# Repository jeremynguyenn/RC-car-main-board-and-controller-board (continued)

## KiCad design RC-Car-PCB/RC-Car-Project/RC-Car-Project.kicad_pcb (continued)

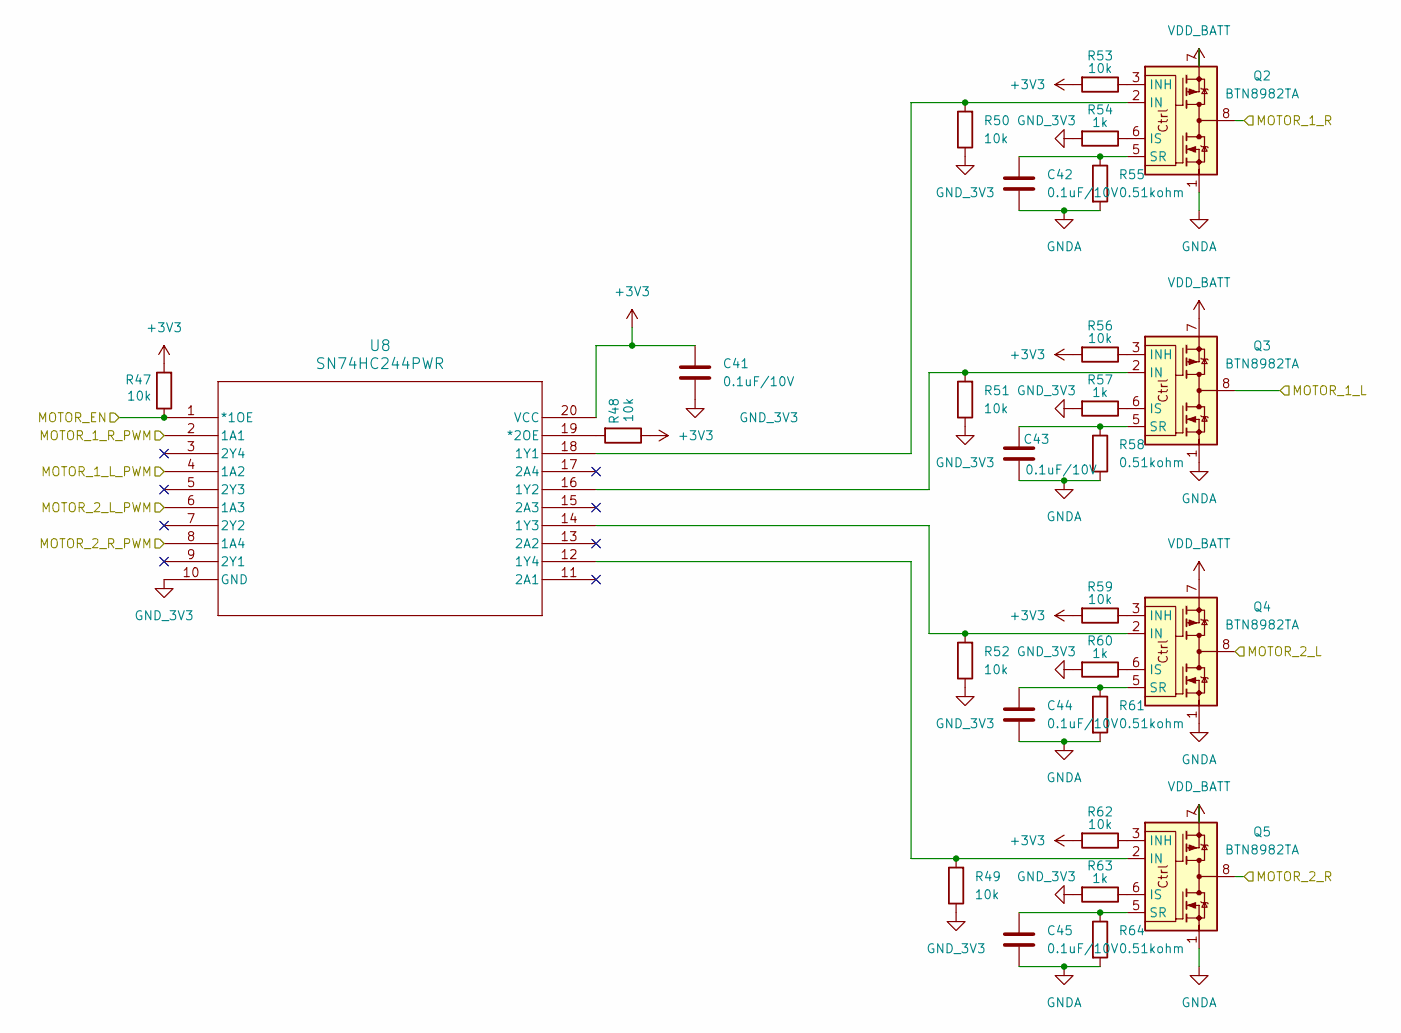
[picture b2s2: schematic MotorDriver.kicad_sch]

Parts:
C41, C42, C43, C44, C45: 0.1uF/10V; C_0603_1608Metric; MANUF_PN C0603C104K5RAC7411
Q2, Q3, Q4, Q5: BTN8982TA; TO-263-7_TabPin8; MANUF_PN BTN8982TAAUMA1
R47, R48, R49, R50, R51, R52, R53, R56, R59, R62: 10k; R_0603_1608Metric; MANUF_PN RC0603FR-0710KL
R54, R57, R60, R63: 1k; R_0603_1608Metric; MANUF_PN RMCF0603FT1K00
R55, R58, R61, R64: 0.51kohm; R_0603_1608Metric; MANUF_PN RMCF0603FT510R
U8: SN74HC244PWR; PW20; MANUF_PN SN74HC244PWR

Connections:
+3V3: C41.1, R47.2, R48.1, R53.2, R56.2, R59.2, R62.2, U8.20 (VCC); also elsewhere on the board
/Connectors/M1_LEFT: Q3.4, Q3.8; also elsewhere on the board
/Connectors/M1_RIGHT: Q2.4, Q2.8; also elsewhere on the board
/Connectors/M2_LEFT: Q4.4, Q4.8; also elsewhere on the board
/Connectors/M2_RIGHT: Q5.4, Q5.8; also elsewhere on the board
/MCU/LEFT_PWM1: U8.4 (1A2); also elsewhere on the board
/MCU/LEFT_PWM2: U8.6 (1A3); also elsewhere on the board
/MCU/MOTOR_EN: R47.1, U8.1 (*1OE); also elsewhere on the board
/MCU/RIGHT_PWM1: U8.2 (1A1); also elsewhere on the board
/MCU/RIGHT_PWM2: U8.8 (1A4); also elsewhere on the board
GNDA: C41.2, C42.2, C43.2, C44.2, C45.2, Q2.1, Q3.1, Q4.1, Q5.1, R49.1, R50.1, R51.1, R52.1, R54.2, R55.2, R57.2, R58.2, R60.2, R61.2, R63.2, R64.2, U8.10 (GND); also elsewhere on the board
unnamed: Q2.2 (IN), R50.2, U8.18 (1Y1)
unnamed: Q2.3 (INH), R53.1
unnamed: Q2.6 (IS), R54.1
unnamed: C42.1, Q2.5 (SR), R55.1
unnamed: Q3.2 (IN), R51.2, U8.16 (1Y2)
unnamed: Q3.3 (INH), R56.1
unnamed: Q3.6 (IS), R57.1
unnamed: C43.1, Q3.5 (SR), R58.1
unnamed: Q4.2 (IN), R52.2, U8.14 (1Y3)
unnamed: Q4.3 (INH), R59.1
unnamed: Q4.6 (IS), R60.1
unnamed: C44.1, Q4.5 (SR), R61.1
unnamed: Q5.2 (IN), R49.2, U8.12 (1Y4)
unnamed: Q5.3 (INH), R62.1
unnamed: Q5.6 (IS), R63.1
unnamed: C45.1, Q5.5 (SR), R64.1
unnamed: R48.2, U8.19 (*2OE)
VDD_BATT: Q2.7, Q3.7, Q4.7, Q5.7; also elsewhere on the board

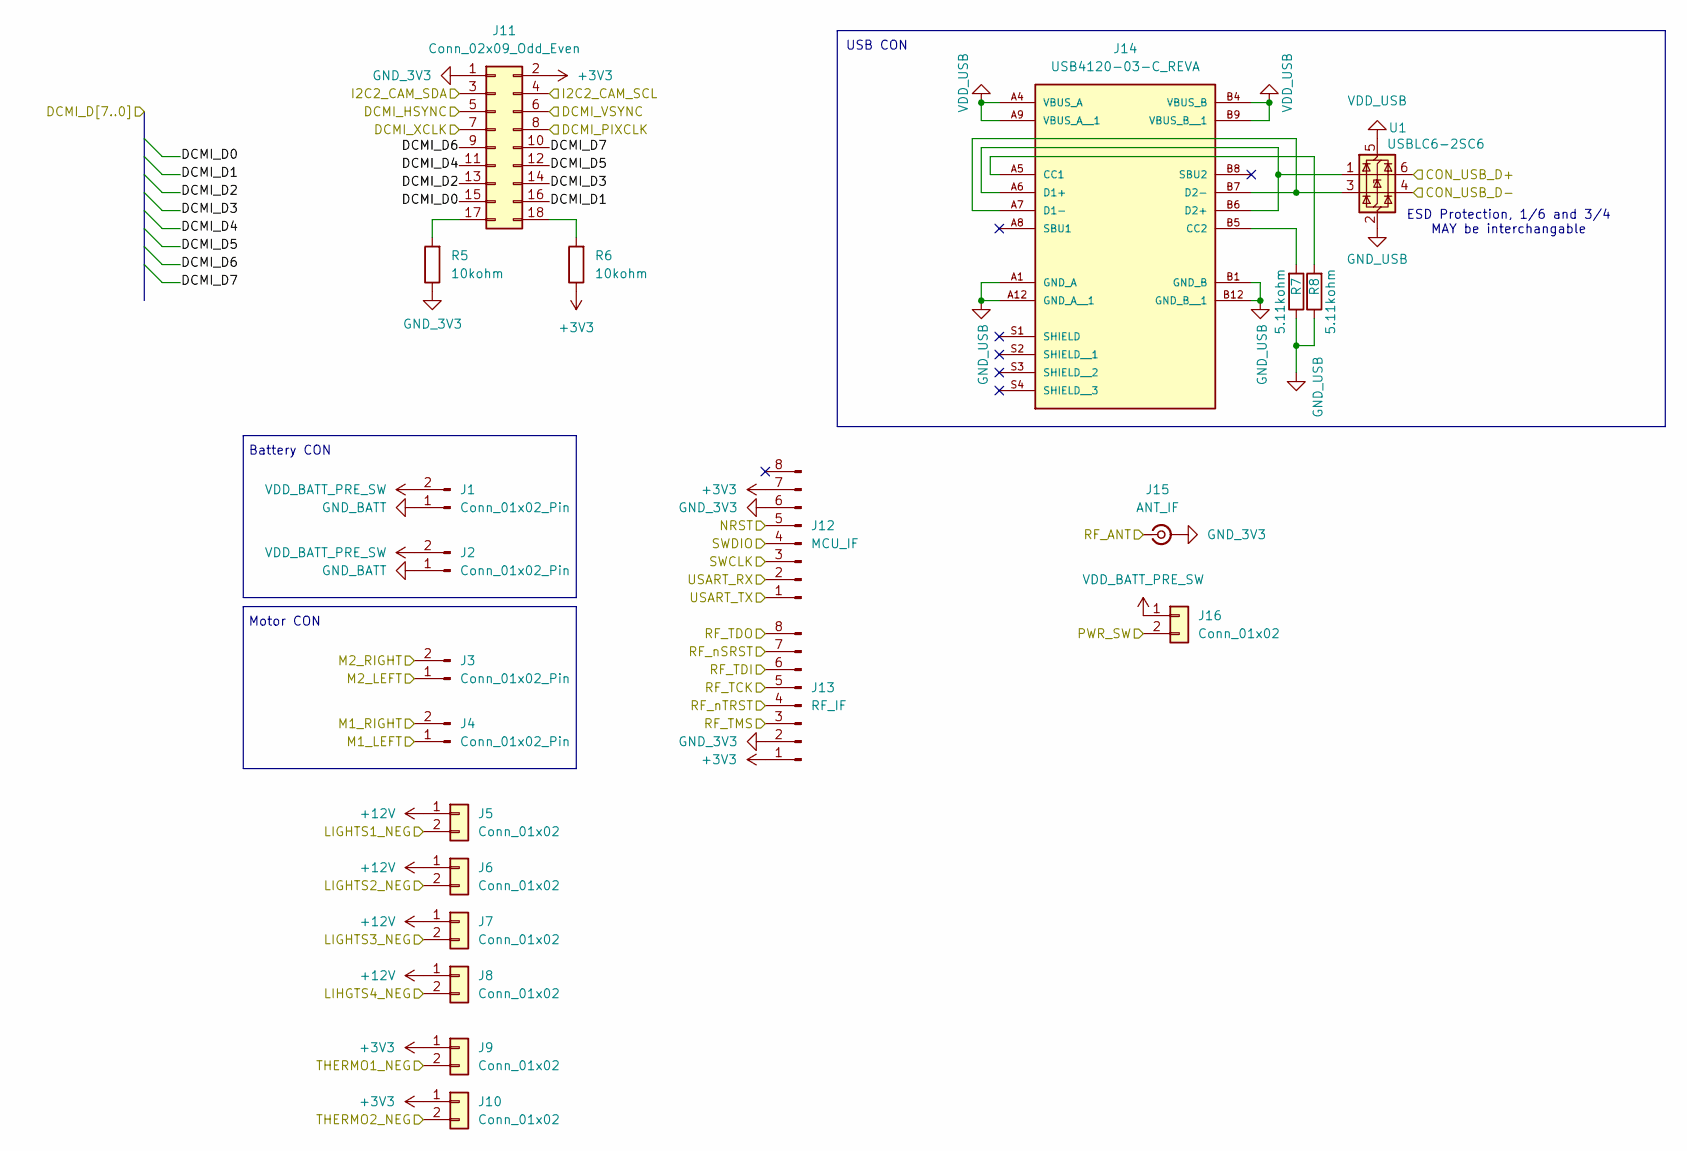
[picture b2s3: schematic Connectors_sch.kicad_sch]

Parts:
J1, J2, J3, J4: Conn_01x02_Pin; AMASS_XT60-M_1x02_P7.20mm_Vertical; MANUF_PN N/A
J5, J6, J7, J8, J9, J10, J16: Conn_01x02; JST_XH_B2B-XH-AM_1x02_P2.50mm_Vertical; MANUF_PN B2B-XH-AM
J11: Conn_02x09_Odd_Even; PinSocket_2x09_P2.54mm_Horizontal; MANUF_PN PPPC092LJBN-RC
J12: MCU_IF; PinHeader_2x04_P2.54mm_Vertical; MANUF_PN PH2-08-UA
J13: RF_IF; PinHeader_2x04_P2.54mm_Vertical; MANUF_PN PH2-08-UA
J14: USB4120-03-C_REVA; GCT_USB4120-03-C_REVA; PARTREV A
J15: ANT_IF; SMA_Molex_73251-1153_EdgeMount_Horizontal; MANUF_PN 0732511153
R5, R6: 10kohm; R_0603_1608Metric; MANUF_PN RC0603FR-0710KL
R7, R8: 5.11kohm; R_0603_1608Metric; MANUF_PN CRCW06035K11FKEAC
U1: USBLC6-2SC6; SOT-23-6; MANUF_PN USBLC6-2SC6

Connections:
+3V3: J9.1, J10.1, J11.2, J12.7, J13.1, R6.1; also elsewhere on the board
+12V: J5.1, J6.1, J7.1, J8.1; also elsewhere on the board
/Connectors/CON_USB_D+: U1.6 (I/O1); also elsewhere on the board
/Connectors/CON_USB_D-: U1.4 (I/O2); also elsewhere on the board
/Connectors/DCMI_D0: J11.15; also elsewhere on the board
/Connectors/DCMI_D1: J11.16; also elsewhere on the board
/Connectors/DCMI_D2: J11.13; also elsewhere on the board
/Connectors/DCMI_D3: J11.14; also elsewhere on the board
/Connectors/DCMI_D4: J11.11; also elsewhere on the board
/Connectors/DCMI_D5: J11.12; also elsewhere on the board
/Connectors/DCMI_D6: J11.9; also elsewhere on the board
/Connectors/DCMI_D7: J11.10; also elsewhere on the board
/Connectors/DCMI_HSYNC: J11.5; also elsewhere on the board
/Connectors/DCMI_PIXCLK: J11.8; also elsewhere on the board
/Connectors/DCMI_VSYNC: J11.6; also elsewhere on the board
/Connectors/DCMI_XCLK: J11.7; also elsewhere on the board
/Connectors/I2C2_CAM_SCL: J11.4; also elsewhere on the board
/Connectors/I2C2_CAM_SDA: J11.3; also elsewhere on the board
/Connectors/LIGHTS1_NEG: J5.2; also elsewhere on the board
/Connectors/LIGHTS2_NEG: J6.2; also elsewhere on the board
/Connectors/LIGHTS3_NEG: J7.2; also elsewhere on the board
/Connectors/LIHGTS4_NEG: J8.2; also elsewhere on the board
/Connectors/M1_LEFT: J4.1; also elsewhere on the board
/Connectors/M1_RIGHT: J4.2; also elsewhere on the board
/Connectors/M2_LEFT: J3.1; also elsewhere on the board
/Connectors/M2_RIGHT: J3.2; also elsewhere on the board
/Connectors/NRST: J12.5; also elsewhere on the board
/Connectors/PWR_SW: J16.2; also elsewhere on the board
/Connectors/RF_ANT: J15.1 (In); also elsewhere on the board
/Connectors/RF_TCK: J13.5; also elsewhere on the board
/Connectors/RF_TDI: J13.6; also elsewhere on the board
/Connectors/RF_TDO: J13.8; also elsewhere on the board
/Connectors/RF_TMS: J13.3; also elsewhere on the board
/Connectors/RF_nSRST: J13.7
/Connectors/RF_nTRST: J13.4; also elsewhere on the board
/Connectors/SWCLK: J12.3; also elsewhere on the board
/Connectors/SWDIO: J12.4; also elsewhere on the board
/Connectors/THERMO1_NEG: J9.2; also elsewhere on the board
/Connectors/THERMO2_NEG: J10.2; also elsewhere on the board
/Connectors/USART_RX: J12.2; also elsewhere on the board
/Connectors/USART_TX: J12.1; also elsewhere on the board
GNDA: J11.1, J12.6, J13.2, J14.A1 (GND_A), J14.A12 (GND_A__1), J14.B1 (GND_B), J14.B12 (GND_B__1), J15.2 (Ext), R5.1, R7.1, R8.1, U1.2 (GND); also elsewhere on the board
GND_BATT: J1.1, J2.1; also elsewhere on the board
unnamed: J11.17, R5.2
unnamed: J11.18, R6.2
unnamed: J14.A5 (CC1), R8.2
unnamed: J14.B5 (CC2), R7.2
unnamed: J14.A6 (D1+), J14.B6 (D2+), U1.1 (I/O1)
unnamed: J14.A7 (D1-), J14.B7 (D2-), U1.3 (I/O2)
VDD_BATT_PRE_SW: J1.2, J2.2, J16.1; also elsewhere on the board
VDD_USB: J14.A4 (VBUS_A), J14.A9 (VBUS_A__1), J14.B4 (VBUS_B), J14.B9 (VBUS_B__1), U1.5 (VBUS); also elsewhere on the board

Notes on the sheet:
Battery CON
ESD Protection, 1/6 and 3/4 MAY be interchangable
USB CON
Motor CON

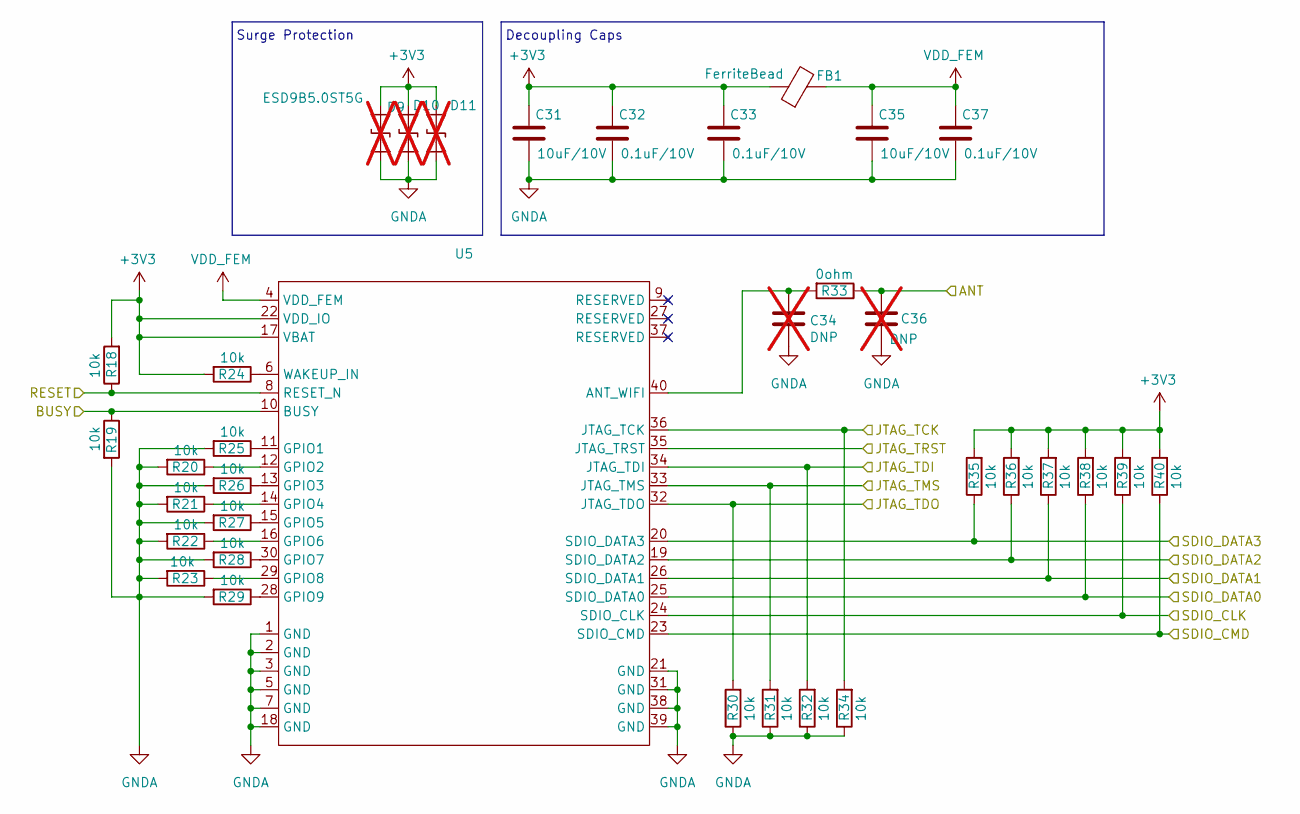
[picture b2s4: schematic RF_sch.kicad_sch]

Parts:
C31, C35: 10uF/10V; C_0603_1608Metric; MANUF_PN CL10A106KP8NNNC
C32, C33, C37: 0.1uF/10V; C_0603_1608Metric; MANUF_PN C0603C104K5RAC7411
C34, C36: DNP; C_0603_1608Metric; MANUF_PN N/A; not fitted
D9, D10, D11: ESD9B5.0ST5G; D_SOD-923; MANUF_PN N/A; not fitted
FB1: FerriteBead; C_0603_1608Metric; MANUF_PN HCB 1608KF-181T20
R18, R19, R20, R21, R22, R23, R24, R25, R26, R27, R28, R29, R30, R31, R32, R34, R35, R36, R37, R38, R39, R40: 10k; C_0603_1608Metric; MANUF_PN RC0603FR-0710KL
R33: 0ohm; R_0603_1608Metric; MANUF_PN RMCF0603ZT0R00
U5: FGH100MABMD; MANUF_PN FGH100MABMD

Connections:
+3V3: C31.1, C32.1, C33.1, D9.2 (A2), D10.2 (A2), D11.2 (A2), FB1.1, R18.2, R24.2, R35.2, R36.2, R37.2, R38.2, R39.2, R40.2, U5.17 (VBAT), U5.22 (VDD_IO); also elsewhere on the board
/Connectors/RF_ANT: C36.1, R33.1; also elsewhere on the board
/Connectors/RF_TCK: R34.2, U5.36 (JTAG_TCK); also elsewhere on the board
/Connectors/RF_TDI: R32.2, U5.34 (JTAG_TDI); also elsewhere on the board
/Connectors/RF_TDO: R30.2, U5.32 (JTAG_TDO); also elsewhere on the board
/Connectors/RF_TMS: R31.2, U5.33 (JTAG_TMS); also elsewhere on the board
/Connectors/RF_nTRST: U5.35 (JTAG_TRST); also elsewhere on the board
/MCU/RF_RESET: R18.1, U5.8 (RESET_N); also elsewhere on the board
/MCU/SDMMC1_CK: R39.1, U5.24 (SDIO_CLK); also elsewhere on the board
/MCU/SDMMC1_CMD: R40.1, U5.23 (SDIO_CMD); also elsewhere on the board
/MCU/SDMMC1_D0: R38.1, U5.25 (SDIO_DATA0); also elsewhere on the board
/MCU/SDMMC1_D1: R37.1, U5.26 (SDIO_DATA1); also elsewhere on the board
/MCU/SDMMC1_D2: R36.1, U5.19 (SDIO_DATA2); also elsewhere on the board
/MCU/SDMMC1_D3: R35.1, U5.20 (SDIO_DATA3); also elsewhere on the board
/RF/BUSY: R19.1, U5.10 (BUSY)
GNDA: C31.2, C32.2, C33.2, C34.2, C35.2, C36.2, C37.2, D9.1 (A1), D10.1 (A1), D11.1 (A1), R19.2, R20.2, R21.2, R22.2, R23.2, R25.2, R26.2, R27.2, R28.2, R29.2, R30.1, R31.1, R32.1, R34.1, U5.1 (GND), U5.2 (GND), U5.3 (GND), U5.5 (GND), U5.7 (GND), U5.18 (GND), U5.21 (GND), U5.31 (GND), U5.38 (GND), U5.39 (GND); also elsewhere on the board
unnamed: C34.1, R33.2, U5.40 (ANT_WIFI)
unnamed: R25.1, U5.11 (GPIO1)
unnamed: R20.1, U5.12 (GPIO2)
unnamed: R26.1, U5.13 (GPIO3)
unnamed: R21.1, U5.14 (GPIO4)
unnamed: R27.1, U5.15 (GPIO5)
unnamed: R22.1, U5.16 (GPIO6)
unnamed: R28.1, U5.30 (GPIO7)
unnamed: R23.1, U5.29 (GPIO8)
unnamed: R29.1, U5.28 (GPIO9)
unnamed: R24.1, U5.6 (WAKEUP_IN)
VDD_FEM: C35.1, C37.1, FB1.2, U5.4 (VDD_FEM)

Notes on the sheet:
Decoupling Caps
Surge Protection

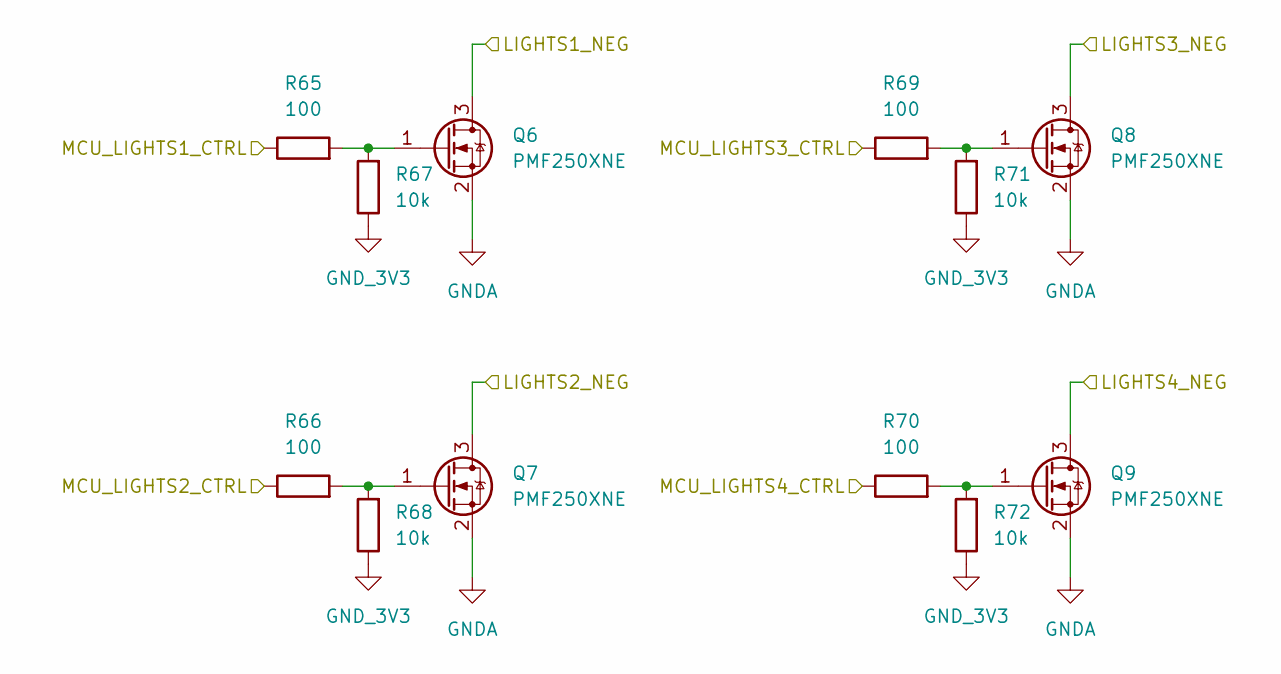
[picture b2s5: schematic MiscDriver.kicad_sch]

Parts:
Q6, Q7, Q8, Q9: PMF250XNE; SOT-23; MANUF_PN PMF250XNEX
R65, R66, R69, R70: 100; R_0603_1608Metric; MANUF_PN RC0603FR-07100RL
R67, R68, R71, R72: 10k; R_0603_1608Metric; MANUF_PN RC0603FR-0710KL

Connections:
/Connectors/LIGHTS1_NEG: Q6.3 (D); also elsewhere on the board
/Connectors/LIGHTS2_NEG: Q7.3 (D); also elsewhere on the board
/Connectors/LIGHTS3_NEG: Q8.3 (D); also elsewhere on the board
/Connectors/LIHGTS4_NEG: Q9.3 (D); also elsewhere on the board
/MCU/LIGHTS1_PWM: R65.1; also elsewhere on the board
/MCU/LIGHTS2_PWM: R66.1; also elsewhere on the board
/MCU/LIGHTS3_PWM: R69.1; also elsewhere on the board
/MCU/LIGHTS4_PWM: R70.1; also elsewhere on the board
GNDA: Q6.2 (S), Q7.2 (S), Q8.2 (S), Q9.2 (S), R67.1, R68.1, R71.1, R72.1; also elsewhere on the board
unnamed: Q6.1 (G), R65.2, R67.2
unnamed: Q7.1 (G), R66.2, R68.2
unnamed: Q8.1 (G), R69.2, R71.2
unnamed: Q9.1 (G), R70.2, R72.2

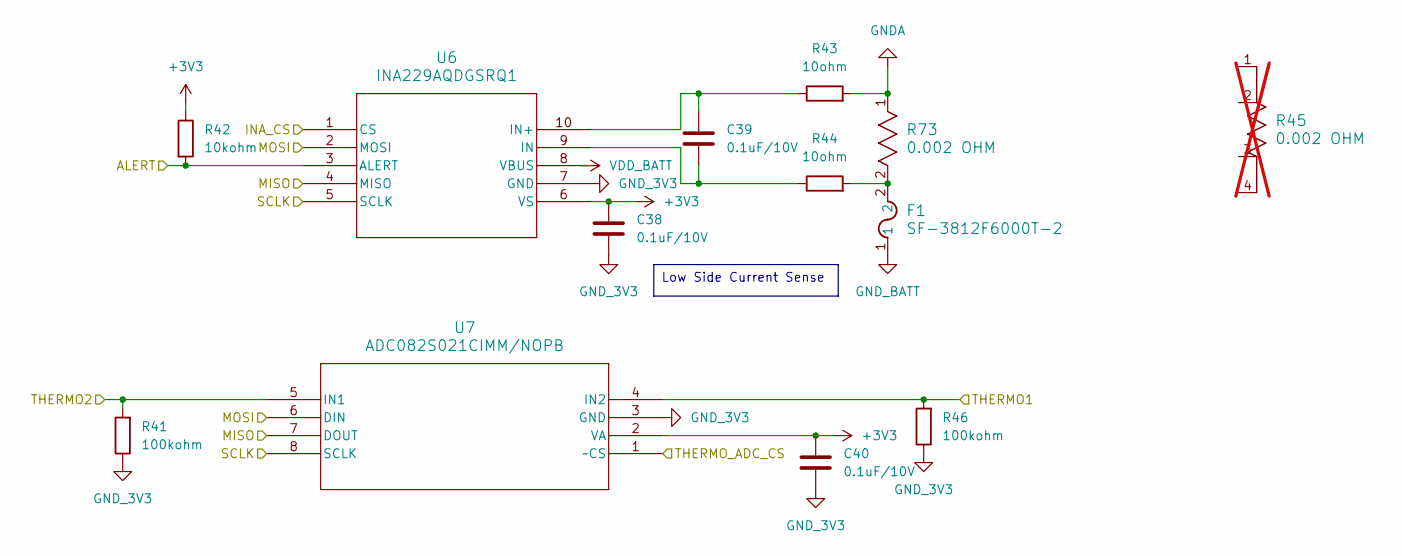
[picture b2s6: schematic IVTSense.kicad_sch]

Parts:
C38, C39, C40: 0.1uF/10V; C_0603_1608Metric; MANUF_PN C0603C104K5RAC7411
F1: SF-3812F6000T-2; FUS_SF-3812F_BRN; MANUF_PN SF-3812F6000T-2
R41, R46: 100kohm; R_0603_1608Metric; MANUF_PN RMCF0603FT100K
R42: 10kohm; R_0603_1608Metric; MANUF_PN RC0603FR-0710KL
R43, R44: 10ohm; R_0603_1608Metric; MANUF_PN RMCF0603FT10R0
R45: 0.002 OHM; WSL2726_VIS; MANUF_PN WSL27262L000FEB; not fitted
R73: 0.002 OHM; RES_WSLP5931_.002OHM_VIS; MANUF_PN WSLP59312L000FEA
U6: INA229AQDGSRQ1; VSSOP10_DGS_TEX; MANUF_PN INA229AQDGSRQ1
U7: ADC082S021CIMM/NOPB; MUA08A; MANUF_PN ADC082S021CIMM/NOPB

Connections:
+3V3: C38.1, C40.1, R42.1, U6.6 (VS), U7.2 (VA); also elsewhere on the board
/Connectors/THERMO1_NEG: R46.2, U7.4 (IN2); also elsewhere on the board
/Connectors/THERMO2_NEG: R41.2, U7.5 (IN1); also elsewhere on the board
/IVTSense/ALERT: R42.2, U6.3 (ALERT); also elsewhere on the board
/IVTSense/INA_CS: U6.1 (CS); also elsewhere on the board
/IVTSense/MISO: U6.4 (MISO), U7.7 (DOUT); also elsewhere on the board
/IVTSense/MOSI: U6.2 (MOSI), U7.6 (DIN); also elsewhere on the board
/IVTSense/SCLK: U6.5 (SCLK), U7.8 (SCLK); also elsewhere on the board
/IVTSense/THERMO_ADC_CS: U7.1 (~CS); also elsewhere on the board
GNDA: C38.2, C40.2, R41.1, R43.2, R46.1, R73.1, U6.7 (GND), U7.3 (GND); also elsewhere on the board
GND_BATT: F1.1; also elsewhere on the board
unnamed: F1.2, R44.2, R73.2
unnamed: C39.2, R44.1, U6.9 (IN)
unnamed: C39.1, R43.1, U6.10 (IN+)
VDD_BATT: U6.8 (VBUS); also elsewhere on the board

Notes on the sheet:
Low Side Current Sense

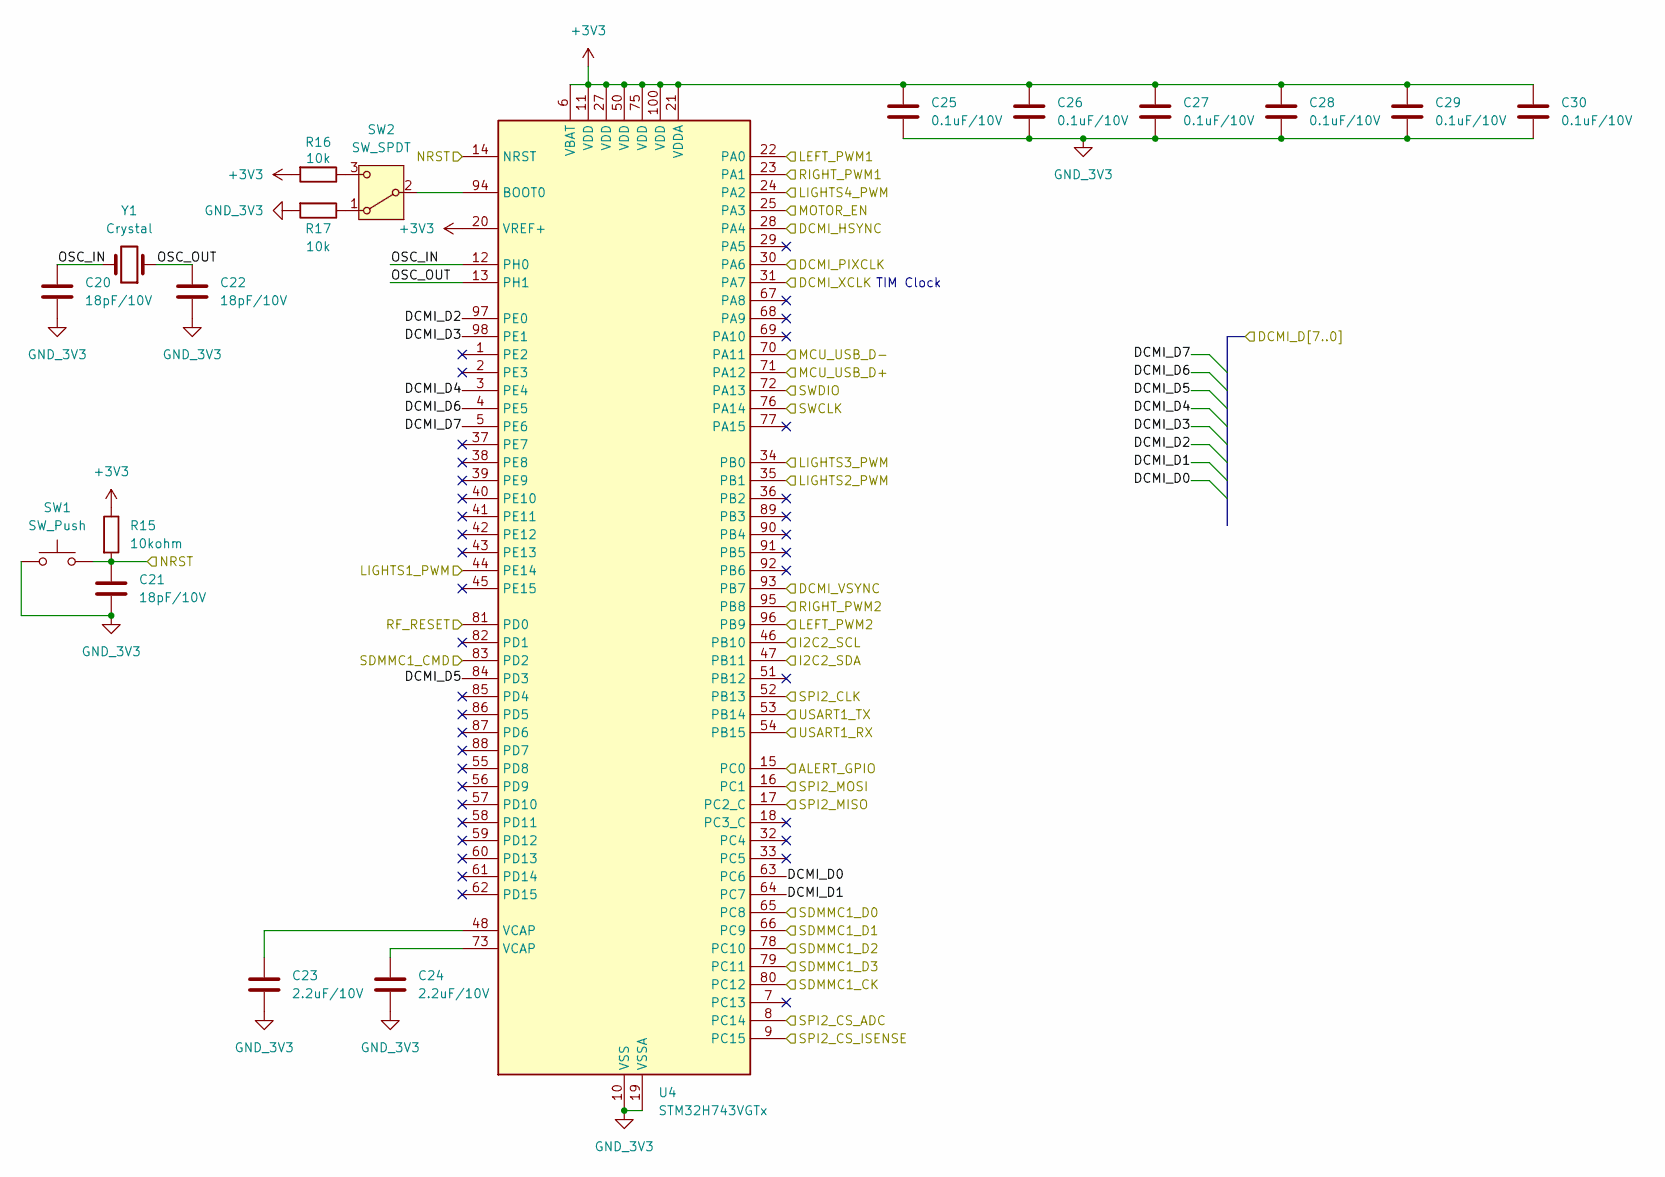
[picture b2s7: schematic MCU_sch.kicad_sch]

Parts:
C20, C21, C22: 18pF/10V; C_0603_1608Metric; MANUF_PN C0603C180J5GACTU
C23, C24: 2.2uF/10V; C_0603_1608Metric; MANUF_PN C0603C225K4PACTU
C25, C26, C27, C28, C29, C30: 0.1uF/10V; C_0603_1608Metric; MANUF_PN C0603C104K5RAC7411
R15: 10kohm; R_0603_1608Metric; MANUF_PN RC0603FR-0710KL
R16, R17: 10k; C_0603_1608Metric; MANUF_PN RC0603FR-0710KL
SW1: SW_Push; SW_PUSH_6mm; MANUF_PN 1825910-6
SW2: SW_SPDT; PinHeader_1x03_P2.54mm_Vertical; MANUF_PN N/A
U4: STM32H743VGTx; LQFP-100_14x14mm_P0.5mm; MANUF_PN STM32H743VGT6
Y1: Crystal; Crystal_SMD_Abracon_ABM3-2Pin_5.0x3.2mm; MANUF_PN ABM7-25.000MHZ-D2Y-T

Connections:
+3V3: C25.1, C26.1, C27.1, C28.1, C29.1, C30.1, R15.1, R16.2, U4.6 (VBAT), U4.11 (VDD), U4.20 (VREF+), U4.21 (VDDA), U4.27 (VDD), U4.50 (VDD), U4.75 (VDD), U4.100 (VDD); also elsewhere on the board
/Connectors/CON_USB_D+: U4.71 (PA12); also elsewhere on the board
/Connectors/CON_USB_D-: U4.70 (PA11); also elsewhere on the board
/Connectors/DCMI_D0: U4.63 (PC6); also elsewhere on the board
/Connectors/DCMI_D1: U4.64 (PC7); also elsewhere on the board
/Connectors/DCMI_D2: U4.97 (PE0); also elsewhere on the board
/Connectors/DCMI_D3: U4.98 (PE1); also elsewhere on the board
/Connectors/DCMI_D4: U4.3 (PE4); also elsewhere on the board
/Connectors/DCMI_D5: U4.84 (PD3); also elsewhere on the board
/Connectors/DCMI_D6: U4.4 (PE5); also elsewhere on the board
/Connectors/DCMI_D7: U4.5 (PE6); also elsewhere on the board
/Connectors/DCMI_HSYNC: U4.28 (PA4); also elsewhere on the board
/Connectors/DCMI_PIXCLK: U4.30 (PA6); also elsewhere on the board
/Connectors/DCMI_VSYNC: U4.93 (PB7); also elsewhere on the board
/Connectors/DCMI_XCLK: U4.31 (PA7); also elsewhere on the board
/Connectors/I2C2_CAM_SCL: U4.46 (PB10); also elsewhere on the board
/Connectors/I2C2_CAM_SDA: U4.47 (PB11); also elsewhere on the board
/Connectors/NRST: C21.1, R15.2, SW1.2, U4.14 (NRST); also elsewhere on the board
/Connectors/SWCLK: U4.76 (PA14); also elsewhere on the board
/Connectors/SWDIO: U4.72 (PA13); also elsewhere on the board
/Connectors/USART_RX: U4.54 (PB15); also elsewhere on the board
/Connectors/USART_TX: U4.53 (PB14); also elsewhere on the board
/IVTSense/ALERT: U4.15 (PC0); also elsewhere on the board
/IVTSense/INA_CS: U4.9 (PC15); also elsewhere on the board
/IVTSense/MISO: U4.17 (PC2_C); also elsewhere on the board
/IVTSense/MOSI: U4.16 (PC1); also elsewhere on the board
/IVTSense/SCLK: U4.52 (PB13); also elsewhere on the board
/IVTSense/THERMO_ADC_CS: U4.8 (PC14); also elsewhere on the board
/MCU/LEFT_PWM1: U4.22 (PA0); also elsewhere on the board
/MCU/LEFT_PWM2: U4.96 (PB9); also elsewhere on the board
/MCU/LIGHTS1_PWM: U4.44 (PE14); also elsewhere on the board
/MCU/LIGHTS2_PWM: U4.35 (PB1); also elsewhere on the board
/MCU/LIGHTS3_PWM: U4.34 (PB0); also elsewhere on the board
/MCU/LIGHTS4_PWM: U4.24 (PA2); also elsewhere on the board
/MCU/MOTOR_EN: U4.25 (PA3); also elsewhere on the board
/MCU/OSC_IN: C20.1, U4.12 (PH0), Y1.2
/MCU/OSC_OUT: C22.1, U4.13 (PH1), Y1.1
/MCU/RF_RESET: U4.81 (PD0); also elsewhere on the board
/MCU/RIGHT_PWM1: U4.23 (PA1); also elsewhere on the board
/MCU/RIGHT_PWM2: U4.95 (PB8); also elsewhere on the board
/MCU/SDMMC1_CK: U4.80 (PC12); also elsewhere on the board
/MCU/SDMMC1_CMD: U4.83 (PD2); also elsewhere on the board
/MCU/SDMMC1_D0: U4.65 (PC8); also elsewhere on the board
/MCU/SDMMC1_D1: U4.66 (PC9); also elsewhere on the board
/MCU/SDMMC1_D2: U4.78 (PC10); also elsewhere on the board
/MCU/SDMMC1_D3: U4.79 (PC11); also elsewhere on the board
GNDA: C20.2, C21.2, C22.2, C23.2, C24.2, C25.2, C26.2, C27.2, C28.2, C29.2, C30.2, R17.2, SW1.1, U4.10 (VSS), U4.19 (VSSA), U4.26 (VSS), U4.49 (VSS), U4.74 (VSS), U4.99 (VSS); also elsewhere on the board
unnamed: C23.1, U4.48 (VCAP)
unnamed: C24.1, U4.73 (VCAP)
unnamed: R17.1, SW2.1 (A)
unnamed: SW2.2 (B), U4.94 (BOOT0)
unnamed: R16.1, SW2.3 (C)

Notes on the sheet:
TIM Clock

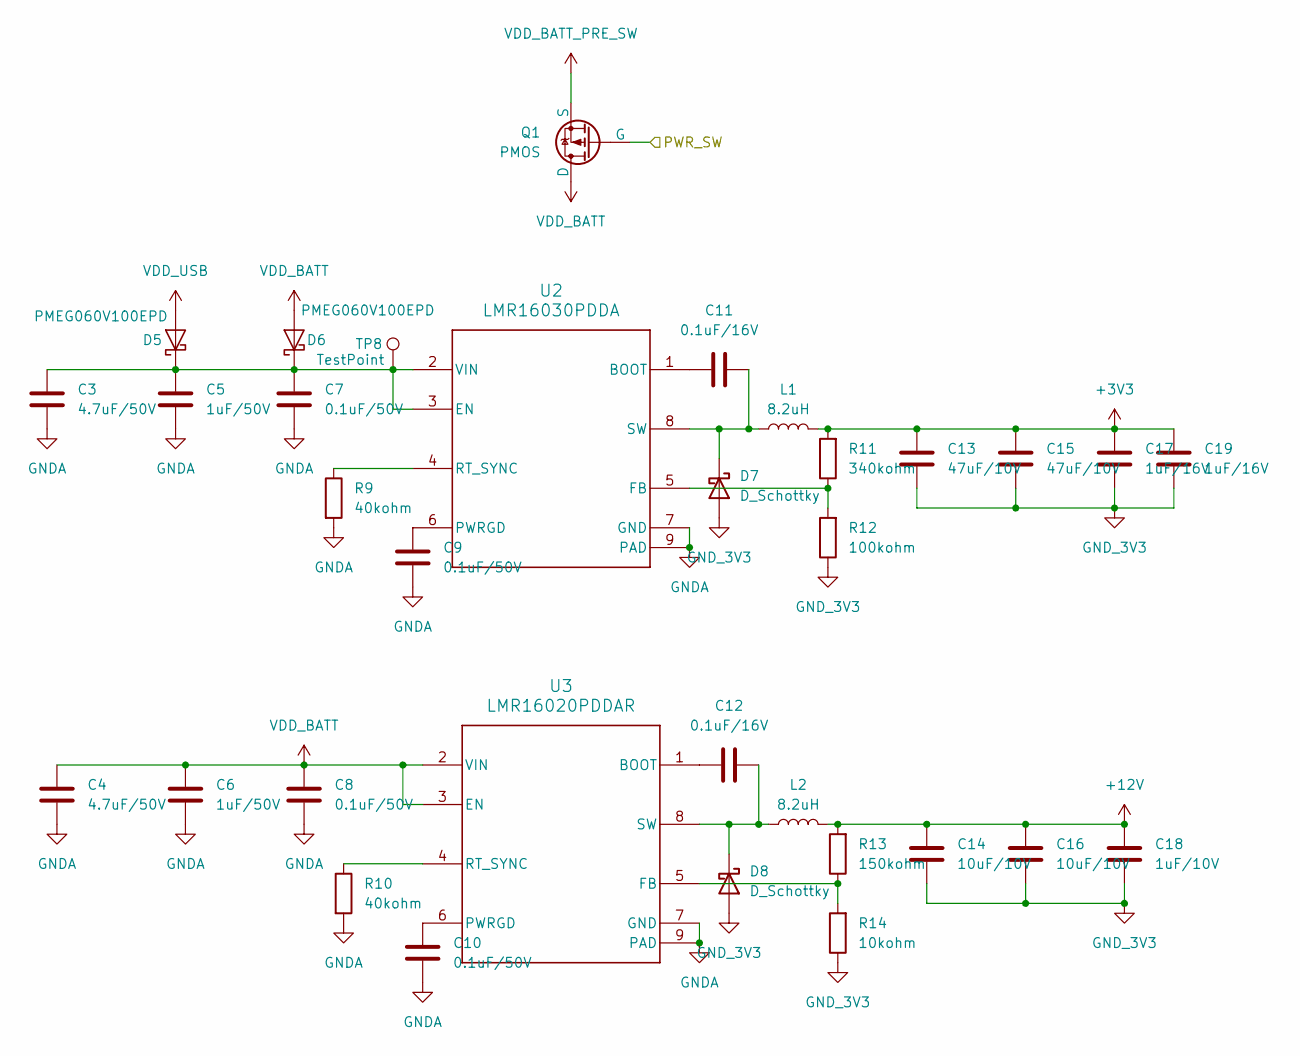
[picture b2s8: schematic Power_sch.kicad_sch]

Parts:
C3, C4: 4.7uF/50V; C_1210_3225Metric; MANUF_PN CL32B475KCVZW6E
C5, C6: 1uF/50V; C_0603_1608Metric; MANUF_PN GRM188D72A105KE01D
C7, C8, C9, C10: 0.1uF/50V; C_0603_1608Metric; MANUF_PN C0603C104K5RAC7411
C11, C12: 0.1uF/16V; C_0603_1608Metric; MANUF_PN C0603C104K5RAC7411
C13, C15: 47uF/10V; C_1210_3225Metric; MANUF_PN LMK325B7476MM-PR
C14, C16: 10uF/10V; C_0603_1608Metric; MANUF_PN CL10A106KP8NNNC
C17, C19: 1uF/16V; C_0603_1608Metric; MANUF_PN CL10B105KO8NNNC
C18: 1uF/10V; C_0603_1608Metric; MANUF_PN CL10B105KO8NNNC
D5, D6: PMEG060V100EPD; Nexperia_CFP15_SOT-1289; MANUF_PN PMEG060V100EPDZ
D7, D8: D_Schottky; Nexperia_CFP3_SOD-123W; MANUF_PN PMEG60T30ELR-QX
L1, L2: 8.2uH; L_Wuerth_MAPI-4030; MANUF_PN 74438357082
Q1: PMOS; TO-220-3_Horizontal_TabDown; MANUF_PN SPP80P06PHXKSA1
R9, R10: 40kohm; R_0603_1608Metric; MANUF_PN RT0603BRD0740KL
R11: 340kohm; R_0603_1608Metric; MANUF_PN RMCF0603FT340K
R12: 100kohm; R_0603_1608Metric; MANUF_PN RMCF0603FT100K
R13: 150kohm; R_0603_1608Metric; MANUF_PN RMCF0603FG150K
R14: 10kohm; R_0603_1608Metric; MANUF_PN RC0603FR-0710KL
TP8: TestPoint; PinHeader_1x02_P2.54mm_Vertical; MANUF_PN N/A
U2: LMR16030PDDA; DDA0008E_N; MANUF_PN LMR16030PDDA
U3: LMR16020PDDAR; DDA0008E_N; MANUF_PN LMR16020PDDAR

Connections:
+3V3: C13.1, C15.1, C17.1, C19.1, L1.2, R11.2; also elsewhere on the board
+12V: C14.1, C16.1, C18.1, L2.2, R13.2; also elsewhere on the board
/Connectors/PWR_SW: Q1.2 (G); also elsewhere on the board
GNDA: C3.2, C4.2, C5.2, C6.2, C7.2, C8.2, C9.2, C10.2, C13.2, C14.2, C15.2, C16.2, C17.2, C18.2, C19.2, D7.2 (A), D8.2 (A), R9.2, R10.2, R12.1, R14.1, U2.7 (GND), U2.9 (PAD), U3.7 (GND), U3.9 (PAD); also elsewhere on the board
unnamed: C3.1, C5.1, C7.1, D5.3 (K), D6.3 (K), TP8.1, U2.2 (VIN), U2.3 (EN)
unnamed: C11.1, D7.1 (K), L1.1, U2.8 (SW)
unnamed: C12.1, D8.1 (K), L2.1, U3.8 (SW)
unnamed: C11.2, U2.1 (BOOT)
unnamed: R11.1, R12.2, U2.5 (FB)
unnamed: C9.1, U2.6 (PWRGD)
unnamed: R9.1, U2.4 (RT_SYNC)
unnamed: C12.2, U3.1 (BOOT)
unnamed: R13.1, R14.2, U3.5 (FB)
unnamed: C10.1, U3.6 (PWRGD)
unnamed: R10.1, U3.4 (RT_SYNC)
VDD_BATT: C4.1, C6.1, C8.1, D6.1 (A), D6.2 (A), Q1.1 (D), U3.2 (VIN), U3.3 (EN); also elsewhere on the board
VDD_BATT_PRE_SW: Q1.3 (S); also elsewhere on the board
VDD_USB: D5.1 (A), D5.2 (A); also elsewhere on the board

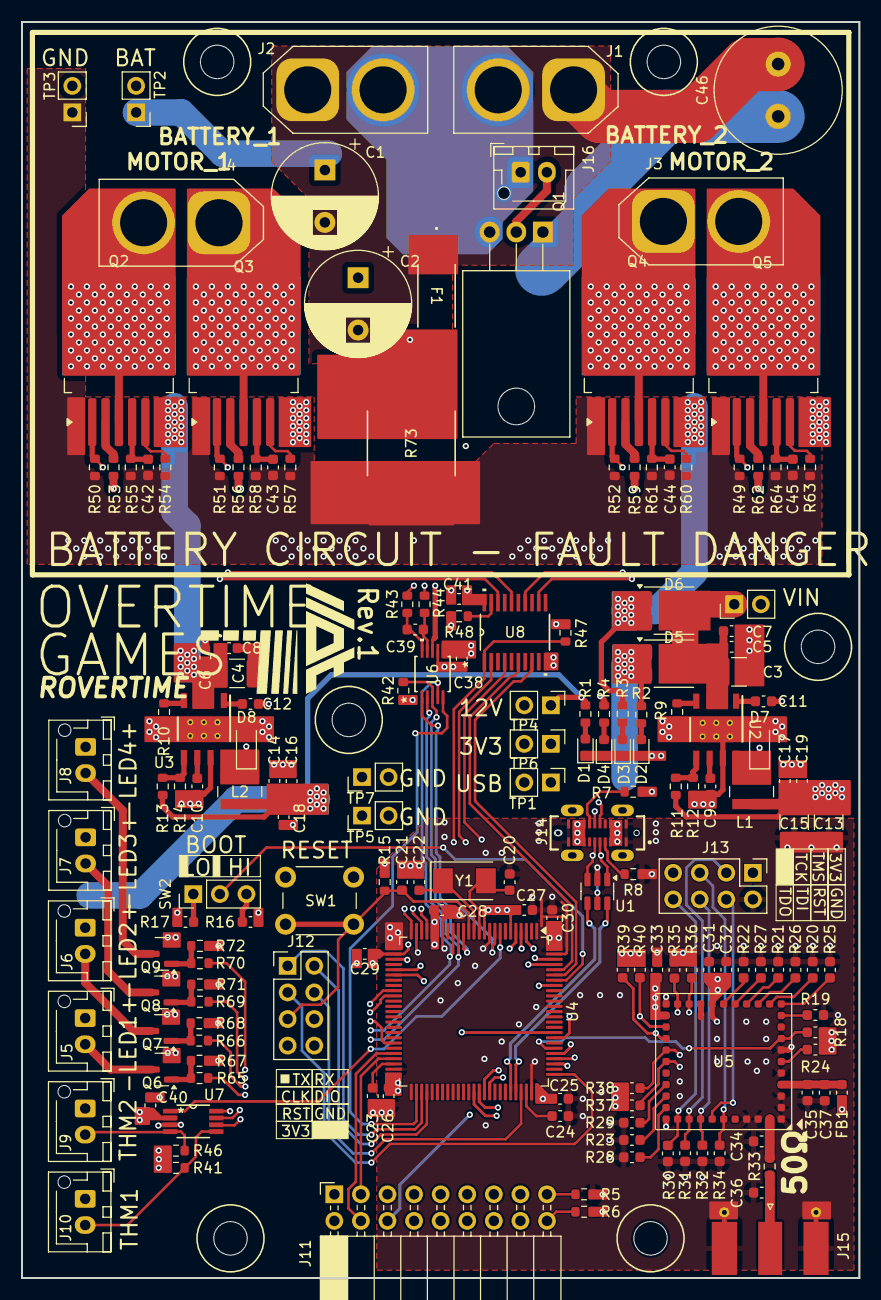
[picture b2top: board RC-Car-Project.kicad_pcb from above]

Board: 4 copper layers, 80.0 x 120.0 mm, 174 parts (0 on the bottom side), 132 nets.

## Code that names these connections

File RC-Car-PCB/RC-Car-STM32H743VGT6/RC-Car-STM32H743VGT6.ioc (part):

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Mcu.Name=STM32H743VGTx
Mcu.Package=LQFP100
Mcu.UserName=STM32H743VGTx
PA0.Signal=S_TIM2_CH1_ETR
PA1.Signal=S_TIM2_CH2
PA11.Mode=Device_Only
PA11.Signal=USB_OTG_FS_DM
PA12.Mode=Device_Only
PA12.Signal=USB_OTG_FS_DP
PA2.Signal=S_TIM2_CH3
PA3.GPIOParameters=PinState
PA3.PinState=GPIO_PIN_SET
PA3.Signal=GPIO_Output
PA4.Mode=Slave_8_bits_External_Synchro
PA4.Signal=DCMI_HSYNC
PA6.Mode=Slave_8_bits_External_Synchro
PA6.Signal=DCMI_PIXCLK
PA7.Signal=S_TIM14_CH1
PB0.Signal=S_TIM3_CH3
PB1.Signal=S_TIM3_CH4
PB10.GPIOParameters=GPIO_Speed,GPIO_Pu
PB10.GPIO_Pu=GPIO_PULLUP
PB10.GPIO_Speed=GPIO_SPEED_FREQ_VERY_HIGH
PB10.Mode=I2C
PB10.Signal=I2C2_SCL
PB11.GPIOParameters=GPIO_Speed,GPIO_Pu
PB11.GPIO_Pu=GPIO_PULLUP
PB11.GPIO_Speed=GPIO_SPEED_FREQ_VERY_HIGH
PB11.Mode=I2C
PB11.Signal=I2C2_SDA
PB13.Mode=Full_Duplex_Master
PB13.Signal=SPI2_SCK
PB14.Mode=Asynchronous
PB14.Signal=USART1_TX
PB15.Mode=Asynchronous
PB15.Signal=USART1_RX
PB7.Mode=Slave_8_bits_External_Synchro
PB7.Signal=DCMI_VSYNC
PB8.Signal=S_TIM4_CH3
PB9.Signal=S_TIM4_CH4
PC0.Signal=GPIO_Input
PC1.Mode=Full_Duplex_Master
PC1.Signal=SPI2_MOSI
PC14-OSC32_IN\ (OSC32_IN).GPIOParameters=PinState,GPIO_Label
PC14-OSC32_IN\ (OSC32_IN).GPIO_Label=ADC_CS
PC14-OSC32_IN\ (OSC32_IN).PinState=GPIO_PIN_SET
PC14-OSC32_IN\ (OSC32_IN).Signal=GPIO_Output
PC15-OSC32_OUT\ (OSC32_OUT).GPIOParameters=GPIO_Speed,PinState,GPIO_Label
PC15-OSC32_OUT\ (OSC32_OUT).GPIO_Label=INA_CS
PC15-OSC32_OUT\ (OSC32_OUT).GPIO_Speed=GPIO_SPEED_FREQ_LOW
PC15-OSC32_OUT\ (OSC32_OUT).PinState=GPIO_PIN_SET
PC15-OSC32_OUT\ (OSC32_OUT).Signal=GPIO_Output
PC2_C.Mode=Full_Duplex_Master
PC2_C.Signal=SPI2_MISO
PC6.Mode=Slave_8_bits_External_Synchro
PC6.Signal=DCMI_D0
PC7.Mode=Slave_8_bits_External_Synchro
PC7.Signal=DCMI_D1
PD0.Signal=GPIO_Output
PD3.Mode=Slave_8_bits_External_Synchro
PD3.Signal=DCMI_D5
PE0.Mode=Slave_8_bits_External_Synchro
PE0.Signal=DCMI_D2
PE1.Mode=Slave_8_bits_External_Synchro
PE1.Signal=DCMI_D3
PE14.Signal=S_TIM1_CH4
PE4.Mode=Slave_8_bits_External_Synchro
PE4.Signal=DCMI_D4
PE5.Mode=Slave_8_bits_External_Synchro
PE5.Signal=DCMI_D6
PE6.Mode=Slave_8_bits_External_Synchro
PE6.Signal=DCMI_D7
PH0-OSC_IN\ (PH0).Mode=HSE-External-Oscillator
PH0-OSC_IN\ (PH0).Signal=RCC_OSC_IN
PH1-OSC_OUT\ (PH1).Mode=HSE-External-Oscillator
PH1-OSC_OUT\ (PH1).Signal=RCC_OSC_OUT
RCC.SYSCLKFreq_VALUE=150000000
RCC.SYSCLKSource=RCC_SYSCLKSOURCE_PLLCLK
board=custom

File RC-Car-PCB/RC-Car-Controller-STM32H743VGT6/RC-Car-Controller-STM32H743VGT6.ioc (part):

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Mcu.Name=STM32H743VGTx
Mcu.Package=LQFP100
Mcu.UserName=STM32H743VGTx
PA11.Mode=Device_Only
PA11.Signal=USB_OTG_FS_DM
PA12.Mode=Device_Only
PA12.Signal=USB_OTG_FS_DP
PA5.GPIOParameters=GPIO_Label
PA5.GPIO_Label=BTN_LB
PA5.Signal=GPIO_Input
PA6.GPIOParameters=GPIO_Label
PA6.GPIO_Label=WIPE_L
PA6.Signal=SharedAnalog_PA6
PB10.GPIOParameters=GPIO_Speed,GPIO_Pu
PB10.GPIO_Pu=GPIO_PULLUP
PB10.GPIO_Speed=GPIO_SPEED_FREQ_VERY_HIGH
PB10.Mode=I2C
PB10.Signal=I2C2_SCL
PB11.GPIOParameters=GPIO_Speed,GPIO_Pu
PB11.GPIO_Pu=GPIO_PULLUP
PB11.GPIO_Speed=GPIO_SPEED_FREQ_VERY_HIGH
PB11.Mode=I2C
PB11.Signal=I2C2_SDA
PB14.Mode=Asynchronous
PB14.Signal=USART1_TX
PB15.Mode=Asynchronous
PB15.Signal=USART1_RX
PB6.Mode=I2C
PB6.Signal=I2C1_SCL
PB9.Mode=I2C
PB9.Signal=I2C1_SDA
PC10.GPIOParameters=PinState,GPIO_Label
PC10.GPIO_Label=SPI4_RST
PC10.PinState=GPIO_PIN_SET
PC10.Signal=GPIO_Output
PC4.GPIOParameters=GPIO_Label
PC4.GPIO_Label=WIPE_R
PC4.Signal=SharedAnalog_PC4
PC5.GPIOParameters=GPIO_Label
PC5.GPIO_Label=BTN_RB
PC5.Signal=GPIO_Input
PC8.GPIOParameters=GPIO_PuPd,GPIO_Label
PC8.GPIO_Label=BTN_LF
PC8.GPIO_PuPd=GPIO_PULLUP
PC8.Signal=GPIO_Input
PC9.GPIOParameters=GPIO_PuPd,GPIO_Label
PC9.GPIO_Label=BTN_RF
PC9.GPIO_PuPd=GPIO_PULLUP
PC9.Signal=GPIO_Input
PE2.GPIOParameters=GPIO_Speed
PE2.GPIO_Speed=GPIO_SPEED_FREQ_VERY_HIGH
PE2.Mode=TX_Only_Simplex_Unidirect_Master
PE2.Signal=SPI4_SCK
PE4.Mode=NSS_Signal_Hard_Output
PE4.Signal=SPI4_NSS
PE5.GPIOParameters=GPIO_Speed,PinState,GPIO_Label
PE5.GPIO_Label=SPI4_DC
PE5.GPIO_Speed=GPIO_SPEED_FREQ_VERY_HIGH
PE5.PinState=GPIO_PIN_SET
PE5.Signal=GPIO_Output
PE6.GPIOParameters=GPIO_Speed
PE6.GPIO_Speed=GPIO_SPEED_FREQ_VERY_HIGH
PE6.Mode=TX_Only_Simplex_Unidirect_Master
PE6.Signal=SPI4_MOSI
PH0-OSC_IN\ (PH0).Mode=HSE-External-Oscillator
PH0-OSC_IN\ (PH0).Signal=RCC_OSC_IN
PH1-OSC_OUT\ (PH1).Mode=HSE-External-Oscillator
PH1-OSC_OUT\ (PH1).Signal=RCC_OSC_OUT
RCC.SYSCLKFreq_VALUE=150000000
RCC.SYSCLKSource=RCC_SYSCLKSOURCE_PLLCLK
board=custom

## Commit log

2025-11-17 Create LICENSE
